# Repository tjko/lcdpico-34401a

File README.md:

# LCDpico-34401a
TFT LCD Driver for HP34401 using RPi Pico 2 (W)

This project is a LCD (TFT) replacement for the original vacuum fluorescent tube (VFD) display on HP/Agilent/Keysight 34401A multimeters.

This project is based on following projects:

- https://github.com/openscopeproject/HP34401a-OLED-FW
- https://github.com/Ian-Johnston/34401A_VS_Display

This project takes slightly different approach as it uses Raspberry Pi Pico 2 W module. This allows network access over WiFi connection. Firmware has support for SSH/Telnet server that provide access to SCPI style command interface. And there is also HTTP server to provide simple GUI to read the front panel remotely.
Additionally LCD display is drawn in graphics mode (16bit colors) allowing use of pre-rendered graphics for the display.
Initial "theme" makes HP 34401A display look like it has "Nixie" tubes as display. Aim is to make custom themes easy to implement (submissions for themes to include would be appreciated).

Since RP2350 has two cores, one core is used to solely monitor the serial communications between front panel and the meter and update the LCD display. While the other is free to handle I/O and all the other tasks.

### Features
- 2D accelerated graphics (using LT768x graphics controller)
  - 16bpp graphics with support for custom themes (see [Themes](themes.md))
  - Double buffered display (no flickering)
- SCPI "like" programming interface (see [Command Reference](commands.md))
- USB and TTL (3.3V) serial console for configuration (NOTE! these should only be used for configuration and be disconnected when using meter for measurements)
- Support for I2C temperature sensors via QWIIC / STEMMA QT connector (support for up to 8 sensors): [Supported Sensors](https://github.com/tjko/pico-sensor-lib/blob/main/README.md)
- WiFi support (if using Pico 2 W)
  - HTTP server with TLS (SSL) support
  - SSH server for console access
  - Telnet server for console access

### Web Interface

When using Pico 2W, it is possible to enable HTTP server that provides simple interface to remotely view meter display.

Interface works by calling JSON "API" (/status.json) every second and updating the web page. If connection is lost for more than 5 seconds, "Connection Lost" message will appear until connection is restored.

### Where Can I get one?

Currently LCDpico is a full "DIY" project. However pre-compiled firmware is available, so if tinkering with the software is not your cup of tea that won't be a problem.

If there is sufficient interest in this project, then "kits" with pre-assembled PCBs (SMT parts) or just PCB and the parts could be made available...

### Parts List

- PCB Kerbers and BOM: [LCDpico for 34401A](boards/34401a/)
- MCU Module: [Raspberry Pi Pico 2 W](https://www.raspberrypi.com/products/raspberry-pi-pico-2/) (or plain "Pico 2" if WiFi functionality is not desired).
- Display Controller (GPU): [ER-PCBA5981-1](https://www.buydisplay.com/download/manual/ER-PCBA5981-1_Datasheet.pdf) (LTLT7680 graphics controller board with FFC & ZIF connectors)
- TFT Panel: [ER-TFT3.71-1](https://www.buydisplay.com/download/manual/ER-TFT3.71-1_Datasheet.pdf)  (3.71" TFT with ST7701S controller)
- Panel mount USB cable that fits in (unused) pre-drilled holes for BNC connectors at 34401A back panel (for updating firmware easily)
- 5V buck converter module (TO-220 form factor)
- 1.0mm 20pin FFC ("flat-flex") cable about 50-80mm long

#### Sources for parts:
- TFT Panel and LT7680 controller: [buydisplay.com](https://www.buydisplay.com/bar-type-3-71-inch-240x960-ips-tft-lcd-display-spi-rgb-interface) [select "No Touch Panel" and "LT7680 Controller Board with FFC and ZIF Connector"]
- USB panel mount cable: [Adafruit](https://www.adafruit.com/product/6069) (requires additional 180-degree USB-C to Micro-USB adapter, for example [Amazon](https://www.amazon.com/Strhowill-Connector-Adapter-Charging-Transfer/dp/B0DR795HHY))
- 1.0mm 20pin FFC cable (50mm): [DigiKey](https://www.digikey.com/en/products/detail/gct/10-20-A-0050-C-4-08-4-T/22247591)

### Connection to 34401A

This display module is meant to be connected to the front panel, where the cable is soldered on the display module PCB.
Connector on main PCB (34401-61602) is W601.

See Ian Johnston's video on how to install his TFT conversion: [[Video -YouTube]](https://www.youtube.com/watch?v=MFfk2P_R7ck) [[Blog]](https://www.ianjohnston.com/index.php/conversions/34401atftconversion)

W601 (34401A)|J1 (lcdpico-34401a)|Notes
----|---------------|-----
 1|1|AGND
 2|3|FPDO
 3|2|+18V
 4|5|IGFPSCK
 5| |FIL1 (not used)
 6|4|IGFPDI
 7| |-18V (not used)
 8|7|IGFPRES (optional)
 9| |AGND
10|6|IGFPINT (optional)
11| |FIL2 (not used)
12| |2.5V (not used)

## Firmware
Firmware is developed in C using the Pico-SDK. Pre-compiled firmware is released when there is new major features or bug fixes.
Firmware is based on firmware for [FanPico](https://github.com/tjko/fanpico).

Latest pre-compiled firmware image can be found here: [Releases](https://github.com/tjko/lcdpico-34401a/releases)

To get latest firmware with latest updates/fixes you must compile the firmware from the sources.

### Installing firmware image
Firmware can be installed via the built-in UF2 bootloader on the Raspberry Pi Pico or using the debug header with Picoprobe, etc...

#### Selecting Right Firmware to use
Each release (zip file) contains multiple different firmware files.
Make sure to select firmware for the board you're using and for the pico model ("pico_w" if using Pico W).

Firmware filenames use format: lcdpico-<board_model>-<pico_model>.uf2
```
lcdpico-34401A-pico2_w.uf2
```

#### Upgrading Firmware
Firmware upgrade steps:
* Boot Pico into UF2 bootloader. This can be done in two ways:
  1)  Press and hold "bootsel" button and then press and release "reset" button.
  2)  Issue command: SYS:UPGRADE
* Copy firmware file to the USB mass storage device that appears.
* As soon as firmware copy is complete, Pico will reboot and run the lcdpico firmware.

### Building Firmware Images

Raspberry Pi Pico C/C++ SDK is required for compiling the firmware:

##### Install Pico SDK
Pico SDK must be installed working before you can compile fanpico.

Instructions on installing Pico SDK see: [Getting started with Raspberry Pi Pico](https://datasheets.raspberrypi.com/pico/getting-started-with-pico.pdf)

(Make sure PICO_SDK_PATH environment variable is set)

##### Downloading sources

Create some directory for building lcdpico ('src' used in this example):
```
$ mkdir src
$ cd src
$ git clone https://github.com/tjko/lcdpico-34401a.git
$ git submodule update --init --recursive
```

##### Building the firmware

To build lcdpico firmware, first create a build directory:
```
$ cd lcdpico-34401a
$ mkdir build
$ cd build
$ cmake ..
```

Then compile firmware:
```
$ make -j
```

After successful compile you should see firmware binary in the build directory:
sub-directory:

```
$ ls *.uf2
lcdpico.uf2
```

If you have picotool installed you can check the firmware image information:
```
$ picotool info -a lcdpico.uf2
File lcdpico.uf2 family ID 'rp2350-arm-s':

Program Information
 name:                lcdpico
 version:             1.0.2
 web site:            https://kokkonen.net/lcdpico/
 description:         LCDpico-34401A Display Controller
 features:            USB stdin / stdout
 boot settings:       bootdelay = 0
                      safemode = 0
                      sysclock = 0
 binary start:        0x10000000
 binary end:          0x101eff14
 embedded drive:      0x103bf000-0x103fd000 (248K): littlefs flags 0x0033 rw
 embedded drive:      0x103fd000-0x103ff000 (8K): btflashbank flags 0x0033 rw
 target chip:         RP2350
 image type:          ARM Secure

Fixed Pin Information
 0:                   TTL Serial: TX
 1:                   TTL Serial: RX
 2:                   I2C: SDA
 3:                   I2C: SCL
 4:                   DMM: DO
 5:                   LCD SPI: CS
 6:                   LCD SPI: SCK
 7:                   LCD SPI: TX
 9:                   LCM Reset
 10:                  LCM Backlight (PWM)
 11:                  LCM Interrupt
 12:                  LCM SPI: RX
 13:                  LCM SPI: CS
 14:                  LCM SPI: SCK
 15:                  LCM SPI: TX
 16:                  DMM: DI
 18:                  DMM: SCK
 19:                  DMM: INT
 20:                  DMM: RST
 25:                  On-board LED (output)

Build Information
 sdk version:         2.3.1
 pico_board:          pico2_w
 boot2_name:          boot2_w25q080
 build date:          Oct 21 2026
 build attributes:    Release

Metadata Block 1
 address:             0x10000138
 next block address:  0x101eff00
 block type:          image def
 target chip:         RP2350
 image type:          ARM Secure
 extra security:      not enabled

Metadata Block 2
 address:             0x101eff00
 next block address:  0x10000138
 block type:          ignored
```

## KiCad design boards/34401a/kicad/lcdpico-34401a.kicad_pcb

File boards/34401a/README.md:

# LCDPICO-34401A PCB

PCB Size: 125.0mm x 37.2mm

## Notes

Parts list (bill of materials) is here: [BOM](bom.csv)

- Optional parts: R1, SW1, J1, J2, J6
- Recommended parts: C5 (film capacitor), C3 & C4 (install one tantalum 22uF 16V tantalum or two 10uF 16V ones)

## Change Log

v1.1
- Add mounting holes to align board better (so that there is space for Micro-USB to USB-C adapter)
- Switch to 4-layer PCB

v1.0
- First Prototye

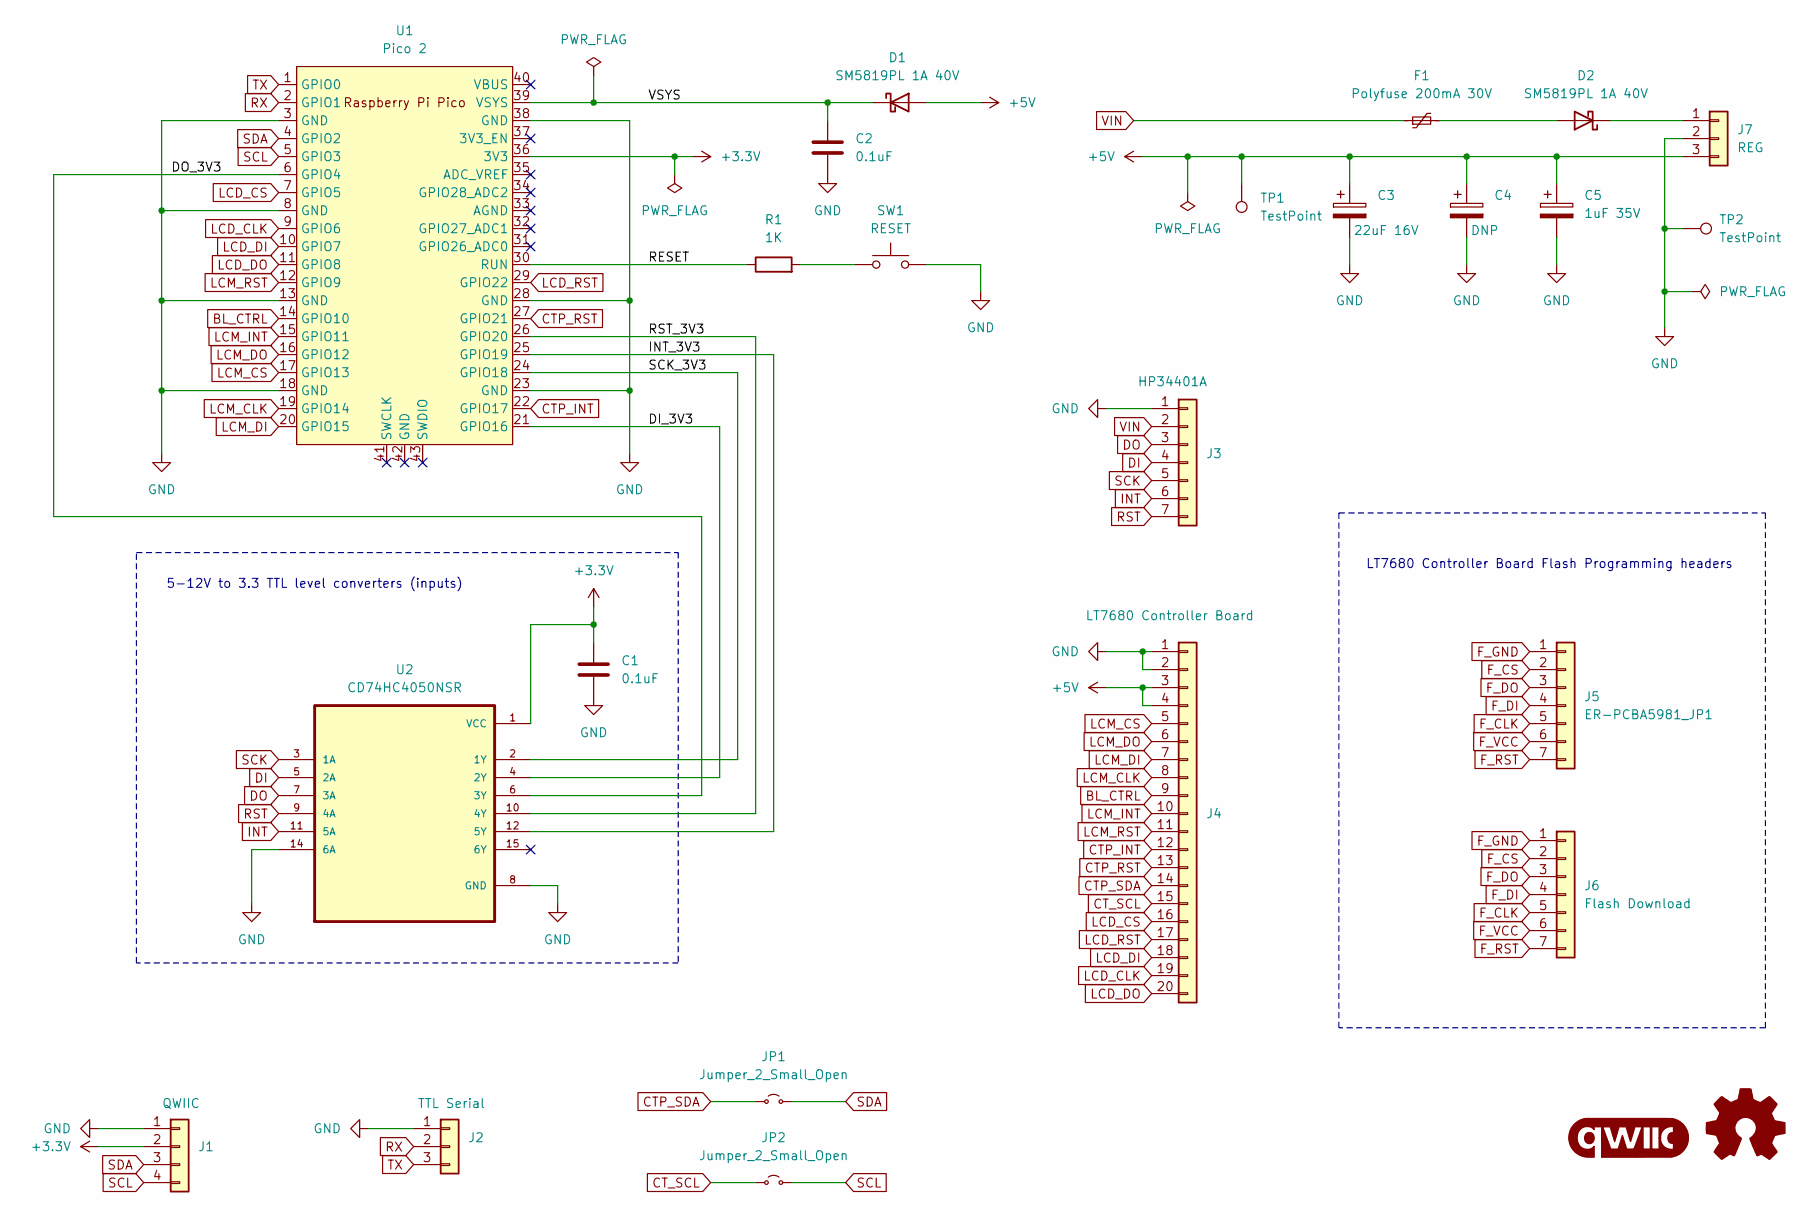
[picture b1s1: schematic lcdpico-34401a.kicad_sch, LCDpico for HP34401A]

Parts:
C1, C2: 0.1uF; C_0603_1608Metric_Pad1.08x0.95mm_HandSolder; Manufacturer Part Number CL10B104KB8NNNC; DigiKey 1276-1000-1-ND
C3: 22uF 16V; CP_EIA-3528-21_Kemet-B_HandSolder; Manufacturer Part Number T491B226K016AT; DigiKey 399-8312-1-ND
C4: DNP; CP_EIA-3528-21_Kemet-B_HandSolder; Manufacturer Part Number T491B226K016AT; DigiKey 399-8312-1-ND
C5: 1uF 35V; C_1210_3225Metric_Pad1.33x2.70mm_HandSolder; Manufacturer Part Number 35MU105KB13225; DigiKey 1189-35MU105KB13225CT-ND
D1, D2: SM5819PL 1A 40V; D_SMA; Manufacturer Part Number SM5819PL-TP; DigiKey SM5819PL-TPMSCT-ND
F1: Polyfuse 200mA 30V; Fuse_1206_3216Metric_Pad1.42x1.75mm_HandSolder; Manufacturer Part Number 0ZCJ0020FF2E; DigiKey 5923-0ZCJ0020FF2ECT-ND
G1: qwiic_Logo
J1: QWIIC; JST_SH_SM04B-SRSS-TB_1x04-1MP_P1.00mm_Horizontal; Manufacturer Part Number SM04B-SRSS-TB(LF)(SN); DigiKey 455-SM04B-SRSS-TBCT-ND
J2: TTL Serial; PinHeader_1x03_P2.54mm_Vertical; Manufacturer Part Number PZ254V-11-03P; LCSC C2937625
J3: HP34401A; PinHeader_1x07_P2.54mm_Vertical; Manufacturer Part Number PZ254V-11-07P; LCSC C492406
J4: LT7680 Controller Board; TE_2-84952-0_1x20-1MP_P1.0mm_Horizontal; Manufacturer Part Number FFC3B07-20-T; DigiKey 2073-FFC3B07-20-TCT-ND or A100319CT-ND
J5: ER-PCBA5981_JP1; PinHeader_2x05_7pin_P2.54mm_Vertical
J6: Flash Download; PinHeader_1x07_P2.54mm_Horizontal
J7: REG; TO-220-3_Horizontal_TabDown_NoHole
JP1, JP2: Jumper_2_Small_Open; SolderJumper-2_P1.3mm_Open_TrianglePad1.0x1.5mm
R1: 1K; R_0603_1608Metric_Pad0.98x0.95mm_HandSolder; Manufacturer Part Number RC0603FR-071KL; LCSC C22548
SW1: RESET; SW-SMD_L3.9-W3.0-P4.45; Manufacturer Part Number TS-1088-AR02016; LCSC C720477
TP1, TP2: TestPoint; TestPoint_Pad_D1.5mm
U1: Pico 2; RPi_Pico_PicoW_SMD_TH
U2: CD74HC4050NSR; SOIC-16_3.9x9.9mm_P1.27mm; Manufacturer Part Number CD74HC4050M96; DigiKey 296-14529-1-ND

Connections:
+3.3V: C1.1, J1.2, U1.36 (3V3), U2.1 (VCC)
+5V: C3.1, C4.1, C5.1, D1.2 (A), J4.3, J4.4, J7.3, TP1.1 (1_1)
/DI_3V3: U1.21 (GPIO16), U2.4 (2Y)
/DO_3V3: U1.6 (GPIO4), U2.6 (3Y)
/INT_3V3: U1.25 (GPIO19), U2.12 (5Y)
/RESET: R1.1, U1.30 (RUN)
/RST_3V3: U1.26 (GPIO20), U2.10 (4Y)
/SCK_3V3: U1.24 (GPIO18), U2.2 (1Y)
/VSYS: C2.1, D1.1 (K), U1.39 (VSYS)
BL_CTRL: J4.9, U1.14 (GPIO10)
CTP_INT: J4.12, U1.22 (GPIO17)
CTP_RST: J4.13, U1.27 (GPIO21)
CTP_SDA: J4.14, JP1.1 (A)
CT_SCL: J4.15, JP2.1 (A)
DI: J3.4, U2.5 (2A)
DO: J3.3, U2.7 (3A)
F_CLK: J5.5, J6.5
F_CS: J5.2, J6.2
F_DI: J5.4, J6.4
F_DO: J5.3, J6.3
F_GND: J5.1, J6.1
F_RST: J5.7, J6.7
F_VCC: J5.6, J6.6
GND: C1.2, C2.2, C3.2, C4.2, C5.2, J1.1, J2.1, J3.1, J4.1, J4.2, J7.2, SW1.2, TP2.1 (1_1), U1.3 (GND), U1.8 (GND), U1.13 (GND), U1.18 (GND), U1.23 (GND), U1.28 (GND), U1.38 (GND), U2.8 (GND), U2.14 (6A)
INT: J3.6, U2.11 (5A)
LCD_CLK: J4.19, U1.9 (GPIO6)
LCD_CS: J4.16, U1.7 (GPIO5)
LCD_DI: J4.18, U1.10 (GPIO7)
LCD_DO: J4.20, U1.11 (GPIO8)
LCD_RST: J4.17, U1.29 (GPIO22)
LCM_CLK: J4.8, U1.19 (GPIO14)
LCM_CS: J4.5, U1.17 (GPIO13)
LCM_DI: J4.7, U1.20 (GPIO15)
LCM_DO: J4.6, U1.16 (GPIO12)
LCM_INT: J4.10, U1.15 (GPIO11)
LCM_RST: J4.11, U1.12 (GPIO9)
unnamed: D2.2 (A), F1.2
unnamed: D2.1 (K), J7.1
unnamed: R1.2, SW1.1
RST: J3.7, U2.9 (4A)
RX: J2.2, U1.2 (GPIO1)
SCK: J3.5, U2.3 (1A)
SCL: J1.4, JP2.2 (B), U1.5 (GPIO3)
SDA: J1.3, JP1.2 (B), U1.4 (GPIO2)
TX: J2.3, U1.1 (GPIO0)
VIN: F1.1, J3.2

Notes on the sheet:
5-12V to 3.3 TTL level converters (inputs)
LT7680 Controller Board Flash Programming headers

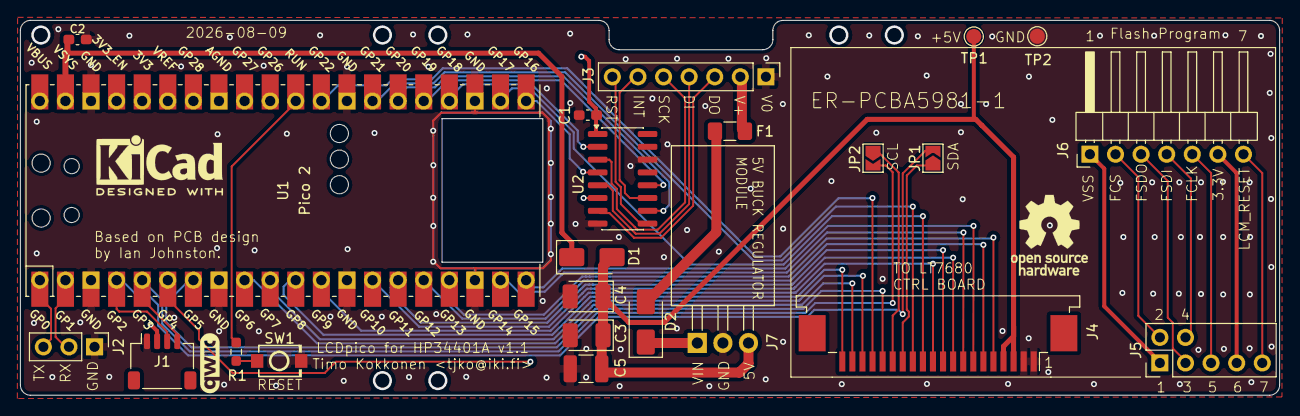
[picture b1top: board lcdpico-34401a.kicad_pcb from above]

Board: 4 copper layers, 125.0 x 37.2 mm, 23 parts (0 on the bottom side), 46 nets.

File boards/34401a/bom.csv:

"Reference","Qty","Value","DNP","Exclude from BOM","Exclude from Board","Footprint","Datasheet","Manufacturer","Manufacturer Part Number","LCSC","DigiKey"
"C1,C2","2","0.1uF","","","","Capacitor_SMD:C_0603_1608Metric_Pad1.08x0.95mm_HandSolder","","Samsung Electro-Mechanics","CL10B104KB8NNNC","C1591","1276-1000-1-ND"
"C3","1","22uF 16V","","","","Capacitor_Tantalum_SMD:CP_EIA-3528-21_Kemet-B_HandSolder","","KEMET","T491B226K016AT","C110051","399-8312-1-ND"
"C4","1","DNP","","","","Capacitor_Tantalum_SMD:CP_EIA-3528-21_Kemet-B_HandSolder","","KEMET","T491B226K016AT","C110051","399-8312-1-ND"
"C5","1","1uF 35V","","","","Capacitor_SMD:C_1210_3225Metric_Pad1.33x2.70mm_HandSolder","","Rubycon","35MU105KB13225","C3780479","1189-35MU105KB13225CT-ND"
"D1,D2","2","SM5819PL 1A 40V","","","","Diode_SMD:D_SMA","","MCC","SM5819PL-TP","C669023","SM5819PL-TPMSCT-ND"
"F1","1","Polyfuse 200mA 30V","","","","Fuse:Fuse_1206_3216Metric_Pad1.42x1.75mm_HandSolder","","Bel Fuse Inc.","0ZCJ0020FF2E","C6964258","5923-0ZCJ0020FF2ECT-ND"
"G1","1","qwiic_Logo","","","Excluded from board","","","","","",""
"J1","1","QWIIC","","","","Connector_JST:JST_SH_SM04B-SRSS-TB_1x04-1MP_P1.00mm_Horizontal","","JST","SM04B-SRSS-TB(LF)(SN)","C160404","455-SM04B-SRSS-TBCT-ND"
"J2","1","TTL Serial","","","","Connector_PinHeader_2.54mm:PinHeader_1x03_P2.54mm_Vertical","","","","",""
"J3","1","HP34401A","","","","Connector_PinHeader_2.54mm:PinHeader_1x07_P2.54mm_Vertical","","","","",""
"J4","1","LT7680 Controller Board","","","","Connector_FFC-FPC:TE_2-84952-0_1x20-1MP_P1.0mm_Horizontal","","GCT","FFC3B07-20-T","C262352","2073-FFC3B07-20-TCT-ND or A100319CT-ND"
"J5","1","ER-PCBA5981_JP1","","","","FanPico:PinHeader_2x05_7pin_P2.54mm_Vertical","","","","",""
"J6","1","Flash Download","","","","Connector_PinHeader_2.54mm:PinHeader_1x07_P2.54mm_Horizontal","","","","",""
"J7","1","REG","","","","FanPico:TO-220-3_Horizontal_TabDown_NoHole","","","","",""
"JP1,JP2","2","Jumper_2_Small_Open","","","","Jumper:SolderJumper-2_P1.3mm_Open_TrianglePad1.0x1.5mm","","","","",""
"R1","1","1K","","","","Resistor_SMD:R_0603_1608Metric_Pad0.98x0.95mm_HandSolder","","YAGEO","RC0603FR-071KL","C22548",""
"SW1","1","RESET","","","","FanPico:SW-SMD_L3.9-W3.0-P4.45","","XUNPU","TS-1088-AR02016","C720477",""
"TP1,TP2","2","TestPoint","","","","TestPoint:TestPoint_Pad_D1.5mm","","","","",""
"U1","1","Pico 2","","","","FanPico:RPi_Pico_PicoW_SMD_TH","","","","",""
"U2","1","CD74HC4050NSR","","","","Package_SO:SOIC-16_3.9x9.9mm_P1.27mm","","TI","CD74HC4050M96","C131932","296-14529-1-ND"

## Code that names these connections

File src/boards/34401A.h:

/* boards/34401A.h */


#define LCDPICO_MODEL     "34401A"


#define LED_PIN 25

#define SENSOR_COUNT 1
#define SENSOR_READ_PIN  -1
#define SENSOR_READ_ADC  ADC_TEMPERATURE_CHANNEL_NUM  /* Internal Temperature sensor */


/* Interface Pins */

/* I2C */
#define I2C_HW    1  /* 0=i2c0, 1=i2c1 */
#define SDA_PIN   2
#define SCL_PIN   3

/* Serial */
#define TX_PIN    0
#define RX_PIN    1


/* LCD Panel SPI interface */
#define LCD_SPI_HW     0  /* 0=spi0, 1=spi1 */
#define LCD_CS_PIN     5
#define LCD_CLK_PIN    6
#define LCD_MOSI_PIN   7
#define LCD_MISO_PIN   -1  // 8
#define LCD_RESET_PIN  -1  // 22

/* LCD Display Controller SPI interface */
#define LCM_SPI_HW     1  /* 0=spi0, 1=spi1 */
#define LCM_CS_PIN     13
#define LCM_CLK_PIN    14
#define LCM_MOSI_PIN   15
#define LCM_MISO_PIN   12
#define LCM_RESET_PIN  9
#define LCM_INT_PIN    11
#define LCM_BL_PIN     10

#define CTP_RESET_PIN  -1 // 21
#define CTP_INT_PIN    -1 // 17

/* Multimeter Front Panel connection */
#define SCK_PIN        18
#define DI_PIN         16
#define DO_PIN         4
#define RST_PIN        20
#define INT_PIN        19

#define TTL_SERIAL   1
#define TTL_SERIAL_UART uart0
#define TTL_SERIAL_SPEED 115200

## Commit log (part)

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2026-06-11 initial fw compiles
2026-06-11 spi testing
2026-06-12 GPU initialization test
2026-06-12 GPU initialization complete
2026-06-13 more testing
2026-06-15 4.53" screen working
2026-06-18 network stuff now compiles
2026-06-20 PNG decoding testing
2026-06-22 Initial graphics assets loading added.
2026-06-22 display demo working
2026-06-23 added indicators
2026-06-25 character overlays added and double buffering
2026-06-25 indicators working
2026-06-29 add protocold decoder
